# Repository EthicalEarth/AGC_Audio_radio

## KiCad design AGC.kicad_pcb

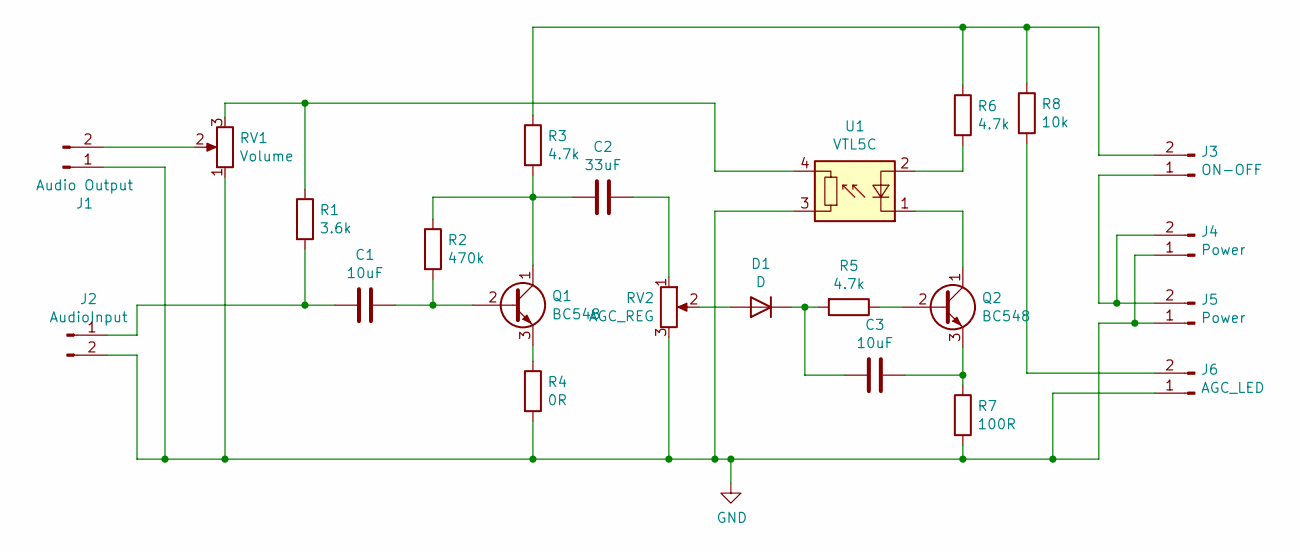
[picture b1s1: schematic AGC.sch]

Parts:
C1, C3: 10uF; C_Radial_D6.3mm_H5.0mm_P2.50mm
C2: 33uF; C_Radial_D6.3mm_H5.0mm_P2.50mm
D1: D; D_A-405_P10.16mm_Horizontal
J1: Audio Output; JST_XH_B2B-XH-A_1x02_P2.50mm_Vertical
J2: AudioInput; JST_XH_B2B-XH-A_1x02_P2.50mm_Vertical
J3: ON-OFF; JST_XH_B2B-XH-A_1x02_P2.50mm_Vertical
J4, J5: Power; JST_XH_B2B-XH-A_1x02_P2.50mm_Vertical
J6: AGC_LED; JST_XH_B2B-XH-A_1x02_P2.50mm_Vertical
Q1, Q2: BC548; TO-92_Inline_Wide
R1: 3.6k; R_Axial_DIN0204_L3.6mm_D1.6mm_P7.62mm_Horizontal
R2: 470k; R_Axial_DIN0204_L3.6mm_D1.6mm_P7.62mm_Horizontal
R3, R5, R6: 4.7k; R_Axial_DIN0204_L3.6mm_D1.6mm_P7.62mm_Horizontal
R4: 0R; R_Axial_DIN0204_L3.6mm_D1.6mm_P7.62mm_Horizontal
R7: 100R; R_Axial_DIN0204_L3.6mm_D1.6mm_P7.62mm_Horizontal
R8: 10k; R_Axial_DIN0204_L3.6mm_D1.6mm_P7.62mm_Horizontal
RV1: Volume; Wago_734-133_1x03_P3.50mm_Vertical
RV2: AGC_REG; Wago_734-133_1x03_P3.50mm_Vertical
U1: VTL5C; PerkinElmer_VTL5C

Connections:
GND: J1.1, J2.2, J4.1, J5.1, J6.1, R4.2, R7.2, RV1.1, RV2.3, U1.3
unnamed: C1.1, Q1.2 (B), R2.2
unnamed: C1.2, J2.1, R1.2
unnamed: C2.1, RV2.1
unnamed: C2.2, Q1.1 (C), R2.1, R3.2
unnamed: C3.1, Q2.3 (E), R7.1
unnamed: C3.2, D1.1 (K), R5.2
unnamed: D1.2 (A), RV2.2
unnamed: J1.2, RV1.2
unnamed: J3.1, J4.2, J5.2
unnamed: J3.2, R3.1, R6.1, R8.1
unnamed: J6.2, R8.2
unnamed: Q1.3 (E), R4.1
unnamed: Q2.1 (C), U1.1 (-)
unnamed: Q2.2 (B), R5.1
unnamed: R1.1, RV1.3, U1.4
unnamed: R6.2, U1.2 (+)

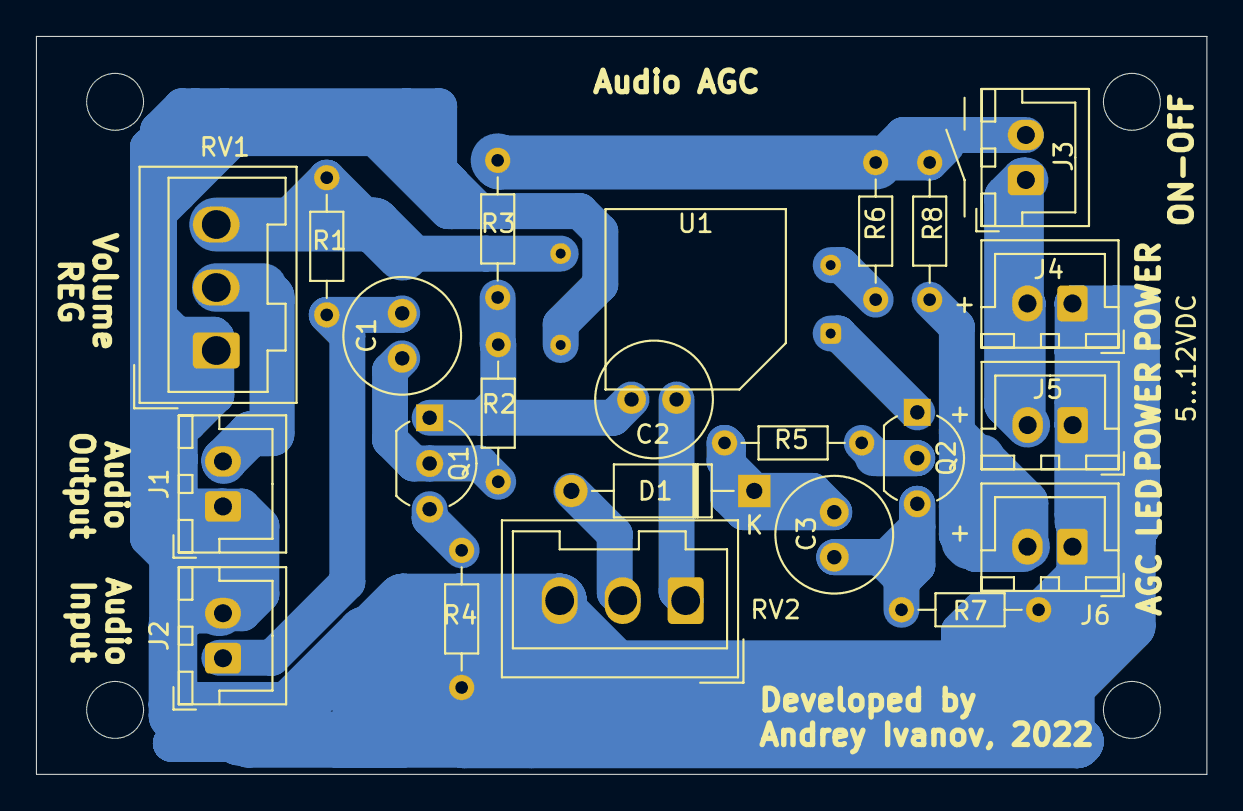
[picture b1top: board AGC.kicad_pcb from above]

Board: 2 copper layers, 65.0 x 41.0 mm, 23 parts (0 on the bottom side), 17 nets.
